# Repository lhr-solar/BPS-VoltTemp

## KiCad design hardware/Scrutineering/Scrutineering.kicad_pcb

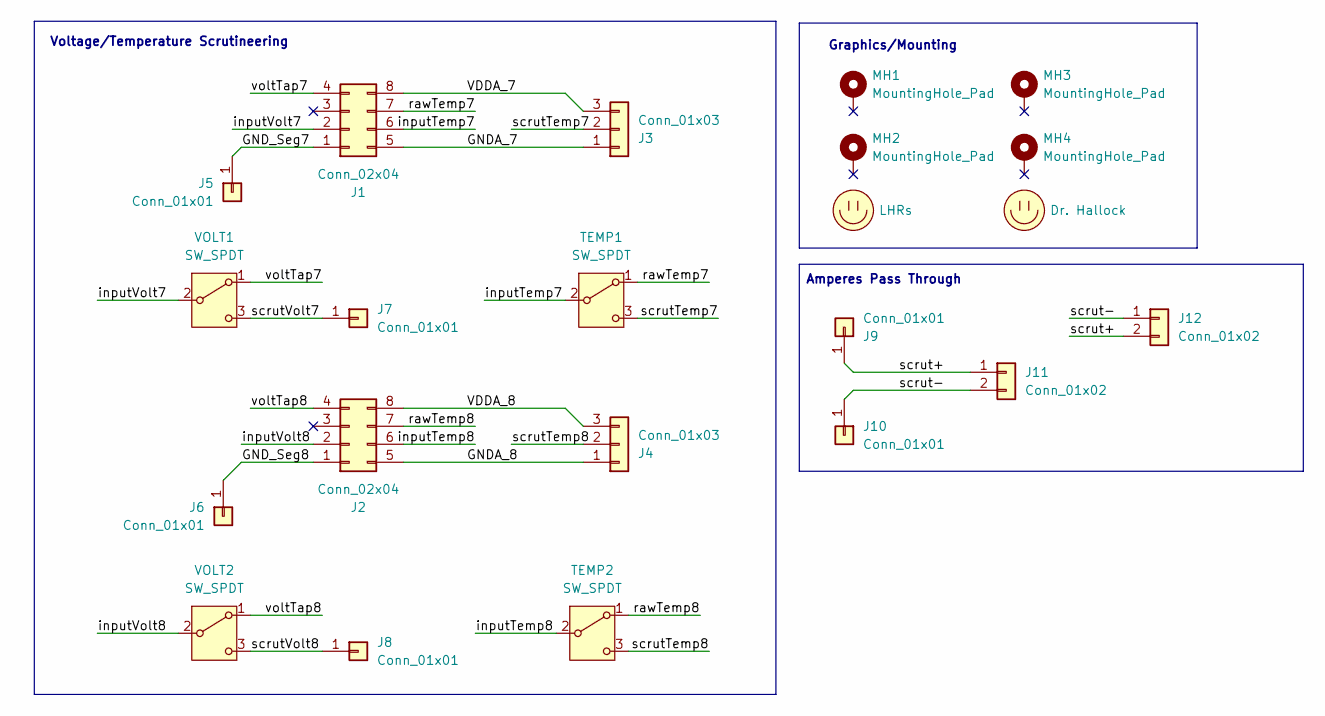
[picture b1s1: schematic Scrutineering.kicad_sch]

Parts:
J1, J2: Conn_02x04; nanofit_02x04
J3, J4: Conn_01x03; 1053131103
J5, J6, J7, J8, J9, J10: Conn_01x01; Banana_Jack_1_Pin_4mm
J11, J12: Conn_01x02; 105313-2102
LOGO1: Dr. Hallock; Hallock_Image_Small
LOGO2: LHRs; LHRs_LOGO
MH1, MH2, MH3, MH4: MountingHole_Pad; MountingHole_3.2mm_M3_Pad_TopBottom
TEMP1, TEMP2: SW_SPDT; SW_Slide_SPDT_Straight_CK_OS102011MS2Q
VOLT1, VOLT2: SW_SPDT; SW_Slide_SPDT_Straight_CK_OS102011MS2Q

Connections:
/GNDA_7: J1.5, J3.1
/GNDA_8: J2.5, J4.1
/GND_Seg7: J1.1, J5.1
/GND_Seg8: J2.1, J6.1
/VDDA_7: J1.8, J3.3
/VDDA_8: J2.8, J4.3
/inputTemp7: J1.6, TEMP1.2 (B)
/inputTemp8: J2.6, TEMP2.2 (B)
/inputVolt7: J1.2, VOLT1.2 (B)
/inputVolt8: J2.2, VOLT2.2 (B)
/rawTemp7: J1.7, TEMP1.1 (A)
/rawTemp8: J2.7, TEMP2.1 (A)
/scrut+: J9.1, J11.1, J12.2
/scrut-: J10.1, J11.2, J12.1
/scrutTemp7: J3.2, TEMP1.3 (C)
/scrutTemp8: J4.2, TEMP2.3 (C)
/scrutVolt7: J7.1, VOLT1.3 (C)
/scrutVolt8: J8.1, VOLT2.3 (C)
/voltTap7: J1.4, VOLT1.1 (A)
/voltTap8: J2.4, VOLT2.1 (A)

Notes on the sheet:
Amperes Pass Through
Voltage/Temperature Scrutineering
Graphics/Mounting

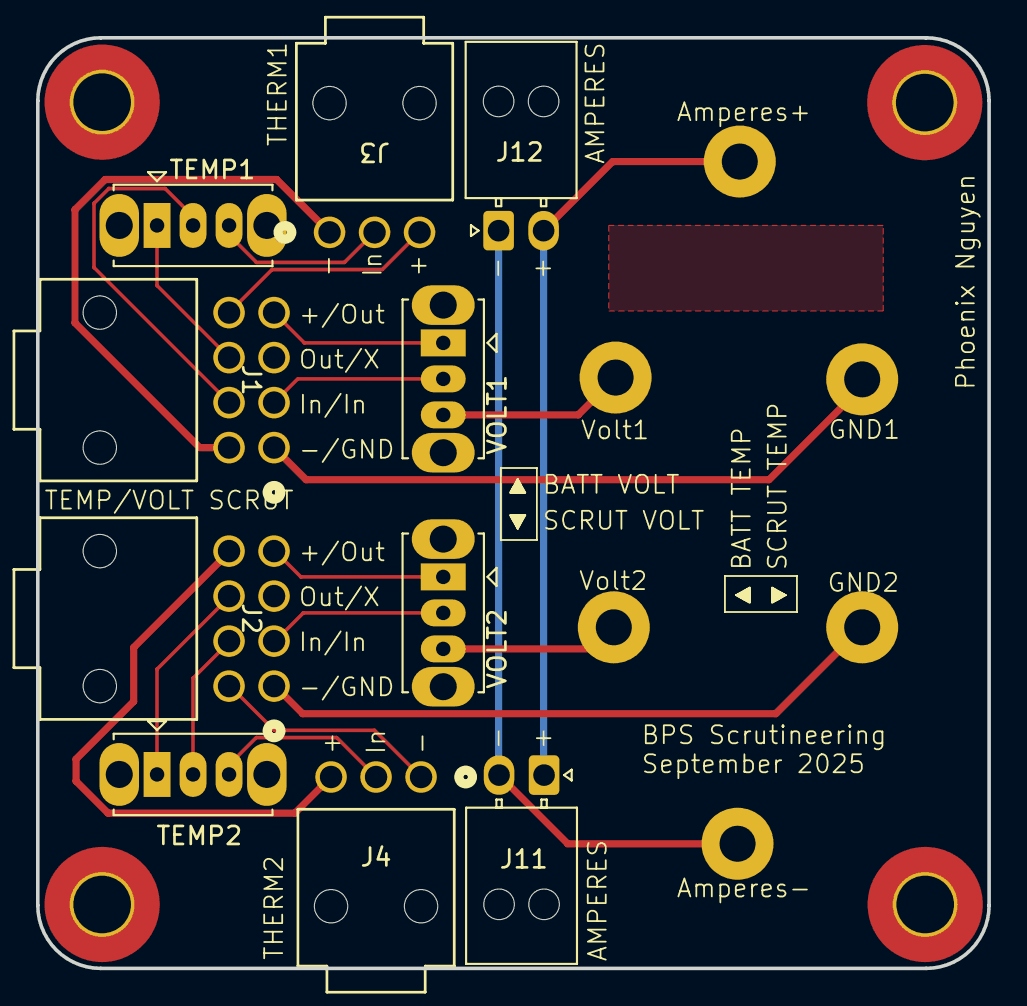
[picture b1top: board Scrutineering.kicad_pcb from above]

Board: 2 copper layers, 52.8 x 51.7 mm, 22 parts (1 on the bottom side), 20 nets.

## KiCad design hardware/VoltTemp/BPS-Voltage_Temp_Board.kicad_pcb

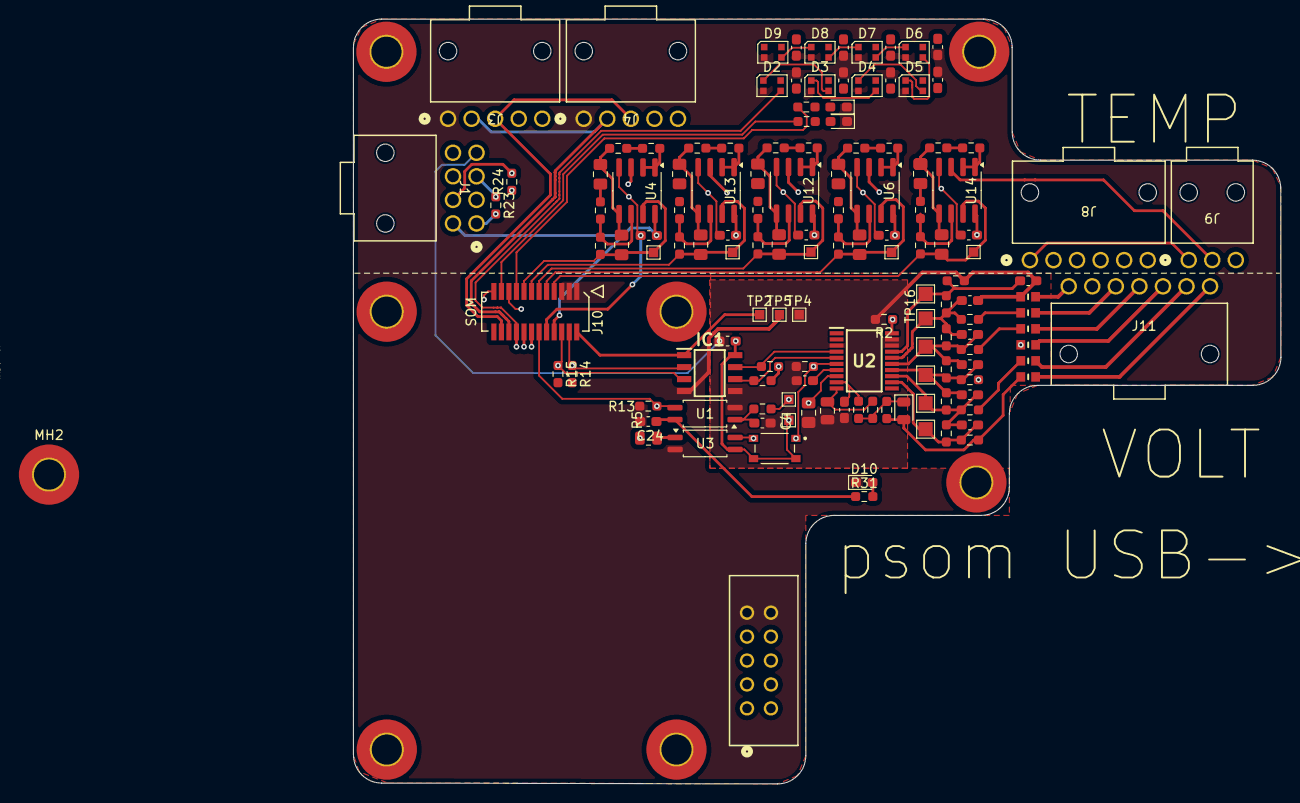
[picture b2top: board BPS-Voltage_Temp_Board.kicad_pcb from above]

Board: 4 copper layers, 98.4 x 81.2 mm, 142 parts (0 on the bottom side), 94 nets.

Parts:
C2: 10μF; C_0805_2012Metric
C3, C26, C28, C29, C32: 1uF; C_0805_2012Metric_Pad1.18x1.45mm_HandSolder
C4: 470pF; C_0603_1608Metric_Pad1.08x0.95mm_HandSolder
C5, C6, C7, C8, C9, C24, C42: 0.1uF; C_0603_1608Metric_Pad1.08x0.95mm_HandSolder
C10, C11, C12, C13, C14, C15, C16, C17: 100nF; C_0603_1608Metric_Pad1.08x0.95mm_HandSolder
C18: 4.7uF; C_0805_2012Metric_Pad1.18x1.45mm_HandSolder
C25, C27, C30, C31, C33: 1.2uF; C_0805_2012Metric_Pad1.18x1.45mm_HandSolder
C34, C35, C36, C37, C38, C39, C40, C41: 1uF; C_0603_1608Metric_Pad1.08x0.95mm_HandSolder
D1: D_Zener_Small; D_0805_2012Metric
D2, D3, D4, D5, D6, D7, D8, D9: WS2812B-2020; LED_WS2812B-2020_PLCC4_2.0x2.0mm
D10: 3v3; LED_0603_1608Metric_Pad1.05x0.95mm_HandSolder
D14: BQ-Fault; LED_0603_1608Metric_Pad1.05x0.95mm_HandSolder
D15: BQ_HB; LED_0603_1608Metric_Pad1.05x0.95mm_HandSolder
F7, F8, F9, F10, F11: 10mA; ptc_fuse_FUSC1607X75N
F12: 40mA; ptc_fuse_FUSC1607X75N
IC1: ISO1641BDR
J1: ScrutineeringConn; nanofit_02x04
J3, J4: Conn_01x05; nanofit_01x05
J5: Logic_Analyzer; CONN_SFH11-xxxC-D05-ST-XX_SUL
J8: Conn_01x06; 1053131106
J9: Conn_01x03; 1053131103
J10: 53307-2471; PeripheralSOM
J11: Conn_01x07; 1053131107
LOGO1: Dr. Hallock; Hallock_Image_Small
LOGO2: LHRs; LHRs_LOGO
MH1, MH2, MH3, MH4: MountingHole_Pad; MountingHole_3.2mm_M3_Pad_TopBottom
R1, R37, R41, R42, R49: 8.2kΩ; R_0603_1608Metric_Pad0.98x0.95mm_HandSolder
R2: 510kΩ; R_0603_1608Metric_Pad0.98x0.95mm_HandSolder
R5: 2kΩ; R_0805_2012Metric
R8, R12: 1kΩ; R_0603_1608Metric_Pad0.98x0.95mm_HandSolder
R9, R10, R11, R13, R14, R15: 10kΩ; R_0603_1608Metric_Pad0.98x0.95mm_HandSolder
R18, R19: 120; R_0603_1608Metric_Pad0.98x0.95mm_HandSolder
R23, R24, R25, R26, R27, R28, R30: 0Ω; R_0603_1608Metric_Pad0.98x0.95mm_HandSolder
R31: 4.3k; R_0603_1608Metric_Pad0.98x0.95mm_HandSolder
R34, R38, R43, R44, R50: 27kΩ; R_0603_1608Metric_Pad0.98x0.95mm_HandSolder
R35, R36, R39, R40, R45, R46, R47, R48, R51, R52: 2.7kΩ; R_0603_1608Metric_Pad0.98x0.95mm_HandSolder
R53, R54, R55, R56, R57, R58, R59, R60: 100Ω; R_0603_1608Metric_Pad0.98x0.95mm_HandSolder
SW1: BOOT; SW_TL3365AF180QG
TP1: TP_Regout; TestPoint_Pad_1.0x1.0mm
TP2, TP5: TestPoint; TestPoint_Pad_1.0x1.0mm
TP3: TP_bmsAlert; TestPoint_Pad_1.0x1.0mm
TP4: bmsGND; TestPoint_Pad_1.0x1.0mm
TP11, TP12, TP13, TP14, TP15: TP_TempOut; TestPoint_Pad_1.0x1.0mm
TP16, TP17, TP18, TP19, TP20, TP21: TestPoint; TestPoint_Pad_1.5x1.5mm
U1, U3: EL3H7
U2: BQ7692003PW
U4, U6, U12, U13, U14: TLV9062xD; SOIC-8_3.9x4.9mm_P1.27mm

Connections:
+3.3V: C10.1, C11.1, C12.1, C13.1, C14.1, C15.1, C16.1, C17.1, C24.1, D2.4 (VDD), D3.4 (VDD), D4.4 (VDD), D5.4 (VDD), D6.4 (VDD), D7.4 (VDD), D8.4 (VDD), D9.4 (VDD), IC1.1 (VCC1), J10.2 (+3.3v), R14.2, R15.2, R31.1, TP2.1, U1.4
+24V: J3.4, J4.4, J10.24 (+24V_In)
/BQ_Fault: J10.21 (SPI1_MISO), R18.1
/BQ_HB: J10.17 (SPI1_MOSI), R19.1
/I-CAN_H: J3.3, J4.3, J10.22 (CAN_H)
/I-CAN_L: J3.2, J4.2, J10.20 (CAN_L)
/LedDin: D2.3 (DIN), J5.1 (CH0), J10.18 (SPI2_SCK)
/PB3: J5.2 (CH1), J10.23 (SPI1_SCK)
/PB14: J5.5 (CH4), J10.14 (SPI2_MISO)
/PB15: J5.3 (CH2), J10.16 (SPI2_MOSI)
/ScrutineeringConn/rawTemperature4_Pre: J1.7, J8.5, R24.1
/ShieldGND: J3.5, J4.5
/TemperatureConn/rawTemperature1: J8.2, U13.3 (+)
/TemperatureConn/rawTemperature2: J8.3, U12.3 (+)
/TemperatureConn/rawTemperature3: J8.4, U6.3 (+)
/TemperatureConn/rawTemperature4: J1.6, R24.2, U4.3 (+)
/TemperatureConn/rawTemperature5: J9.2, U14.3 (+)
/TemperatureFilters/Temperature1: C31.2, J10.13 (ADC1_IN10), R48.2, TP14.1, U13.7
/TemperatureFilters/Temperature2: C30.2, J10.11 (ADC1_IN9), R47.2, TP13.1, U12.7
/TemperatureFilters/Temperature3: C27.2, J10.9 (ADC1_IN7), R40.2, TP12.1, U6.7
/TemperatureFilters/Temperature4: C25.2, J10.15 (ADC1_IN11), R36.2, TP11.1, U4.7
/TemperatureFilters/Temperature5: C33.2, J10.7 (OPAMP1_VINP), R52.2, TP15.1, U14.7
/VoltageConn/1&2COM: F11.2, R54.2
/VoltageConn/1&2COM_ext: F11.1, J11.5
/VoltageConn/2&3COM: F10.2, R55.2
/VoltageConn/2&3COM_ext: F10.1, J11.4
/VoltageConn/3&4COM: F9.2, J1.3, R23.1
/VoltageConn/3&4COM_Out: J1.1, R23.2, R56.2
/VoltageConn/3&4COM_ext: F9.1, J11.3
/VoltageConn/4&5COM: F8.2, R57.2
/VoltageConn/4&5COM_ext: F8.1, J11.2
/VoltageConn/VC0: C34.2, R25.2, R53.1, TP16.1, U2.17 (VC0)
/VoltageConn/VC1: C35.1, C36.2, R25.1, R26.2, R54.1, TP17.1, U2.16 (VC1)
/VoltageConn/VC2: C36.1, C37.2, R26.1, R30.2, R55.1, TP18.1, U2.15 (VC2)
/VoltageConn/VC3: C37.1, C38.2, R27.2, R30.1, R56.1, TP19.1, U2.14 (VC3)
/VoltageConn/VC4: C38.1, C39.2, R27.1, R28.2, R57.1, TP20.1, U2.13 (VC4)
/VoltageConn/VC5: C39.1, R28.1, R58.1, TP21.1, U2.12 (VC5)
/VoltageConn/last_cell: D1.2 (A), F7.2, R12.2, R58.2
/VoltageConn/last_cell_ext: F7.1, J11.1
/VoltageSense/ALERT: R2.1, R59.2, TP3.1, U2.20 (ALERT)
/VoltageSense/BAT: C2.2, R60.2, U2.10 (BAT)
/VoltageSense/I2C_SCL: IC1.3 (SCL1), J5.8 (CH7), J10.6 (I2C1_SCL), R15.1
/VoltageSense/I2C_SDA: IC1.2 (SDA1), J5.7 (CH6), J10.4 (I2C1_SDA), R14.1
/VoltageSense/bmSCL: IC1.6 (SCL2), R10.1, U2.5 (SCL)
/VoltageSense/bmSDA: IC1.7 (SDA2), R9.1, U2.4 (SDA)
/VoltageSense/bmsBoot: R11.2, SW1.1, U2.6 (TS1), U3.4
/VoltageSense/regout: C18.1, C42.1, IC1.8 (VCC2), R9.2, R10.2, SW1.2, TP1.1, U2.8 (REGOUT), U3.3
/bmsAlert: J5.4 (CH3), J10.12 (SPI2_NSS), R13.2, U1.3
/bmsEn: J5.6 (CH5), J10.19 (SPI1_NSS), R5.1
GND: C10.2, C11.2, C12.2, C13.2, C14.2, C15.2, C16.2, C17.2, C24.2, D2.2 (VSS), D3.2 (VSS), D4.2 (VSS), D5.2 (VSS), D6.2 (VSS), D7.2 (VSS), D8.2 (VSS), D9.2 (VSS), D10.1 (K), D14.1 (K), D15.1 (K), IC1.4 (GND1), J3.1, J4.1, J5.9 (GND), J5.10 (GND), J10.1 (GND), J10.3 (GND), J10.5 (GND), R13.1, TP5.1, U3.2
GNDA: C5.2, C6.2, C7.2, C8.2, C9.2, J1.8, J8.6, J9.3, J10.10 (GNDA), U4.4 (V-), U6.4 (V-), U12.4 (V-), U13.4 (V-), U14.4 (V-)
GND_Seg: C2.1, C4.2, C18.2, C34.1, C35.2, C40.2, C41.2, C42.2, F12.2, IC1.5 (GND2), J1.4, R2.2, R11.1, R53.2, TP4.1, U1.2, U2.3 (VSS), U2.18 (SRP), U2.19 (SRN)
unnamed: C3.2, R35.1
unnamed: C4.1, R59.1, U1.1
unnamed: C26.2, R39.1
unnamed: C28.2, R45.1
unnamed: C29.2, R46.1
unnamed: C32.2, R51.1
unnamed: D1.1 (K), R8.2, R12.1, R60.1
unnamed: D2.1 (DOUT), D3.3 (DIN)
unnamed: D3.1 (DOUT), D4.3 (DIN)
unnamed: D4.1 (DOUT), D5.3 (DIN)
unnamed: D5.1 (DOUT), D6.3 (DIN)
unnamed: D6.1 (DOUT), D7.3 (DIN)
unnamed: D7.1 (DOUT), D8.3 (DIN)
unnamed: D8.1 (DOUT), D9.3 (DIN)
unnamed: D10.2 (A), R31.2
unnamed: D14.2 (A), R18.2
unnamed: D15.2 (A), R19.2
unnamed: F12.1, J11.7
unnamed: R1.2, R34.1
unnamed: R5.2, U3.1
unnamed: R37.2, R38.1
unnamed: R41.2, R43.1
unnamed: R42.2, R44.1
unnamed: R49.2, R50.1
unnamed: C41.1, U2.7 (CAP1)
unnamed: C40.1, R8.1, U2.9 (REGSRC)
unnamed: R1.1, U4.1, U4.2 (-)
unnamed: C3.1, C25.1, R34.2, U4.5 (+)
unnamed: R35.2, R36.1, U4.6 (-)
unnamed: R37.1, U6.1, U6.2 (-)
unnamed: C26.1, C27.1, R38.2, U6.5 (+)
unnamed: R39.2, R40.1, U6.6 (-)
unnamed: R41.1, U12.1, U12.2 (-)
unnamed: C28.1, C30.1, R43.2, U12.5 (+)
unnamed: R45.2, R47.1, U12.6 (-)
unnamed: R42.1, U13.1, U13.2 (-)
unnamed: C29.1, C31.1, R44.2, U13.5 (+)
unnamed: R46.2, R48.1, U13.6 (-)
unnamed: R49.1, U14.1, U14.2 (-)
unnamed: C32.1, C33.1, R50.2, U14.5 (+)
unnamed: R51.2, R52.1, U14.6 (-)
VDDA: C5.1, C6.1, C7.1, C8.1, C9.1, J1.5, J8.1, J9.1, J10.8 (VDDA), U4.8 (V+), U6.8 (V+), U12.8 (V+), U13.8 (V+), U14.8 (V+)

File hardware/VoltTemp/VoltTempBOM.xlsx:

Reference | Value | P/N | Footprint | Qty | DNP
D15 | BQ_HB | XL-1608UBC-06A | LED_SMD:LED_0603_1608Metric_Pad1.05x0.95mm_HandSolder | 1
D10 | 3v3 | XL-1608UBC-06A | LED_SMD:LED_0603_1608Metric_Pad1.05x0.95mm_HandSolder | 1
R34,R38,R43,R44,R50 | 27k | TNPU060327K0AYEN00 | Resistor_SMD:R_0603_1608Metric_Pad0.98x0.95mm_HandSolder | 5
U4,U6,U12,U13,U14 | TLV9062xD | TLV9062QDGKRQ1 | Package_SO:SOIC-8_3.9x4.9mm_P1.27mm | 5
SW1 | BOOT | TL3365AF180QG | VoltTemp:SW_TL3365AF180QG | 1
R25,R26,R28,R30 | 0 | SFR03EZPJ000 | Resistor_SMD:R_0603_1608Metric_Pad0.98x0.95mm_HandSolder | 4
R23,R24,R27 | 0 | SFR03EZPJ000 | Resistor_SMD:R_0603_1608Metric_Pad0.98x0.95mm_HandSolder | 3
R35,R36,R39,R40,R45,R46,R47,R48,R51,R52 | 2.7k | SFR03EZPF2701 | Resistor_SMD:R_0603_1608Metric_Pad0.98x0.95mm_HandSolder | 10
J5 | Logic_Analyzer | SFH11-PBPC-D05-ST-BK | UTSVT_Connectors:CONN_SFH11-xxxC-D05-ST-XX_SUL | 1
F7,F8,F9,F10,F11 | 10mA | PTSLR06038V075 | VoltTemp:ptc_fuse_FUSC1607X75N | 5
D14 | BQ-Fault | NCD0603R1 | LED_SMD:LED_0603_1608Metric_Pad1.05x0.95mm_HandSolder | 1
C3,C26,C28,C29,C32,C34,C35,C36,C37,C38,C39,C40,C41 | 1uF | MLASU168SB5105KTNA01 | Capacitor_SMD:C_0603_1608Metric_Pad1.08x0.95mm_HandSolder,Capacitor_SMD:C_0805_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 | 13
C10,C11,C12,C13,C14,C15,C16,C17 | 100nF | MLASH168SB7104KTNA01 | Capacitor_SMD:C_0603_1608Metric_Pad1.08x0.95mm_HandSolder | 8
C5,C6,C7,C8,C9,C24,C42 | 0.1uF | MLASH168SB7104KTNA01 | Capacitor_SMD:C_0603_1608Metric_Pad1.08x0.95mm_HandSolder | 7
IC1 | ISO1641BDR | ISO1641BDR | VoltTemp:ISO1641BDR | 1
C2 | 10uF | GRM21BR61H106KE43K | Capacitor_SMD:C_0805_2012Metric | 1
F12 | 40mA | FUSC1607X75N | VoltTemp:ptc_fuse_FUSC1607X75N | 1
R53,R54,R55,R56,R57,R58,R59,R60 | 100Œ© | ESR03EZPF1000 | Resistor_SMD:R_0603_1608Metric_Pad0.98x0.95mm_HandSolder | 8
R1,R37,R41,R42,R49 | 8.2kŒ© | ERA-3AED822V | Resistor_SMD:R_0603_1608Metric_Pad0.98x0.95mm_HandSolder | 5
U1,U3 | EL3H7 | EL3H7(D)(TA)-VG | UTSVT_ICs:EL3H7 | 2
R31 | 4.3k | CRCW06034K30FKTA | Resistor_SMD:R_0603_1608Metric_Pad0.98x0.95mm_HandSolder | 1
R5 | 2k | CRCW06032K10FKEA | Resistor_SMD:R_0805_2012Metric | 1
R8,R12 | 1k | CRCW06031K00FKEI | Resistor_SMD:R_0603_1608Metric_Pad0.98x0.95mm_HandSolder | 2
R9,R10,R11,R13,R14,R15 | 10k | CRCW060310K0FKEI | Resistor_SMD:R_0603_1608Metric_Pad0.98x0.95mm_HandSolder | 6
R18,R19 | 120 | CRCW0603120RFKEC | Resistor_SMD:R_0603_1608Metric_Pad0.98x0.95mm_HandSolder | 2
R2 | 510k | CPF0603B510KE1 | Resistor_SMD:R_0603_1608Metric_Pad0.98x0.95mm_HandSolder | 1
C25,C27,C30,C31,C33 | 1.2uF | C0805C125K4RACTU | Capacitor_SMD:C_0805_2012Metric_Pad1.18x1.45mm_HandSolder | 5
U2 | BQ7692003PW | BQ7692003PW | VoltTemp:BQ7692003PW | 1
J10 | 53307-2471 | 53307-2471 | UTSVT_Connectors:PeripheralSOM | 1
D1 | D_Zener_Small | 1N448W | Diode_SMD:D_0805_2012Metric | 1
C18 | 4.7uF | 08055D475KAT4A | Capacitor_SMD:C_0805_2012Metric_Pad1.18x1.45mm_HandSolder | 1
C4 | 470pF | 06035C471J4Z2A | Capacitor_SMD:C_0603_1608Metric_Pad1.08x0.95mm_HandSolder | 1
J6,J7,J12,J13 | Conn_01x04 | 1053132104 | VoltTemp:1053132104 | 4
J11 | Conn_01x07 | 1053131107 | VoltTemp:1053131107 | 1
J8 | Conn_01x06 | 1053131106 | VoltTemp:1053131106 | 1
J9 | Conn_01x03 | 1053131103 | VoltTemp:1053131103 | 1
D2,D3,D4,D5,D6,D7,D8,D9 | WS2812B-2020 |  | LED_SMD:LED_WS2812B-2020_PLCC4_2.0x2.0mm | 8

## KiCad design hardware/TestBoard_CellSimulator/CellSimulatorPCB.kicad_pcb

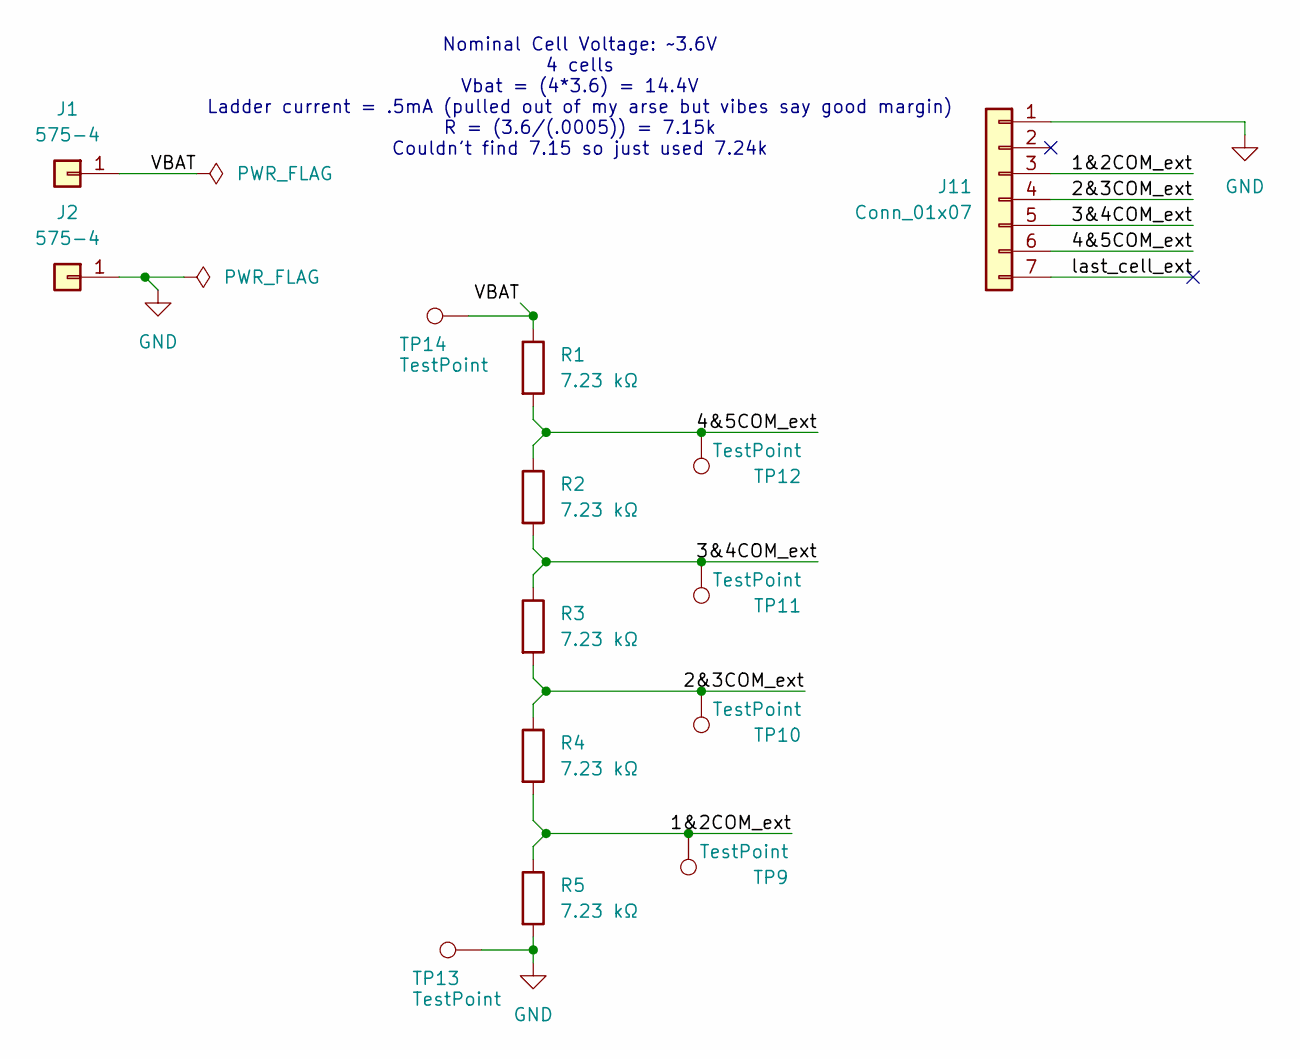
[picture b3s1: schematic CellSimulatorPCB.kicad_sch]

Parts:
J1, J2: 575-4; 5754
J11: Conn_01x07; 1053131107
R1, R2, R3, R4, R5: 7.23 kΩ; R_0603_1608Metric_Pad0.98x0.95mm_HandSolder
TP9, TP10, TP11, TP12, TP13, TP14: TestPoint; TestPoint_Keystone_5005-5009_Compact

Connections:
/1&2COM_ext: J11.3, R4.2, R5.1, TP9.1
/2&3COM_ext: J11.4, R3.2, R4.1, TP10.1
/3&4COM_ext: J11.5, R2.2, R3.1, TP11.1
/4&5COM_ext: J11.6, R1.2, R2.1, TP12.1
/VBAT: J1.1, R1.1, TP14.1
/last_cell_ext: J11.7
GND: J2.1, J11.1, R5.2, TP13.1

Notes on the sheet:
Nominal Cell Voltage: ~3.6V 4 cells Vbat = (4*3.6) = 14.4V Ladder current = .5mA (pulled out of my arse but vibes say good margin) R = (3.6/(.0005)) = 7.15k Couldn't find 7.15 so just used 7.24k

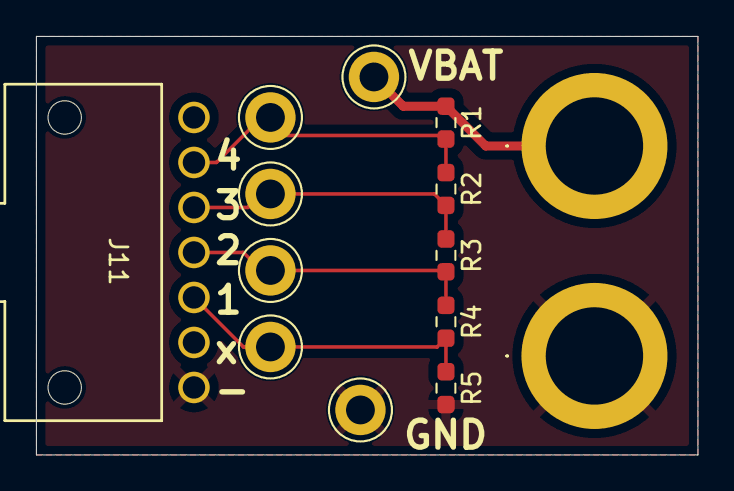
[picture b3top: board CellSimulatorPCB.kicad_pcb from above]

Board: 2 copper layers, 36.8 x 23.2 mm, 14 parts (0 on the bottom side), 6 nets.

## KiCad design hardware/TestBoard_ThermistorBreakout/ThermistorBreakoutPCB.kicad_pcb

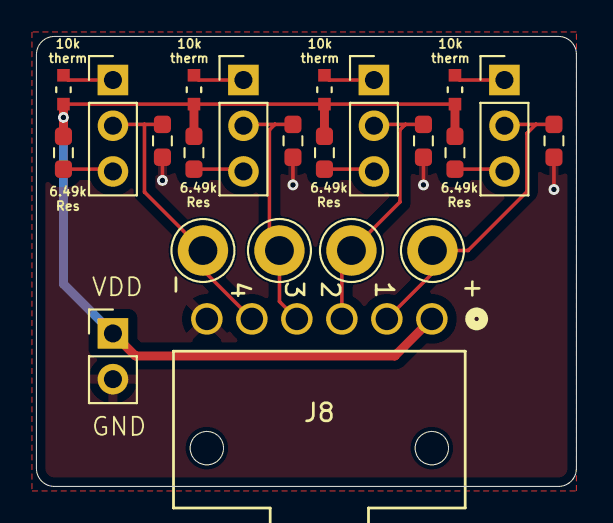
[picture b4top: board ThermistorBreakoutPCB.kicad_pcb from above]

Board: 2 copper layers, 30.0 x 25.0 mm, 22 parts (0 on the bottom side), 14 nets.

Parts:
J1: Conn_01x02; PinHeader_1x02_P2.54mm_Vertical
J3, J4, J5, J6: Conn_01x03; PinHeader_1x03_P2.54mm_Vertical
J8: Conn_01x06; 1053131106
R5, R6, R7, R8, R9, R10, R11, R12: 6.49k; R_0603_1608Metric_Pad0.98x0.95mm_HandSolder
TH5, TH6, TH7, TH8: Thermistor_NTC; THERM_ERT-J1VR104FM
TP8, TP9, TP10, TP11: TestPoint; TestPoint_Keystone_5005-5009_Compact

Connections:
/Temperature1: J3.2, J8.2, R6.1, TP11.1
/Temperature2: J4.2, J8.3, R7.1, TP10.1
/Temperature3: J5.2, J8.4, R9.1, TP8.1
/Temperature4: J6.2, J8.5, R10.1, TP9.1
GNDA: J1.2, J8.6, R6.2, R7.2, R9.2, R10.2
unnamed: J3.1, TH5.2
unnamed: J3.3, R5.1
unnamed: J4.1, TH6.2
unnamed: J4.3, R8.1
unnamed: J5.1, TH7.2
unnamed: J5.3, R11.1
unnamed: J6.1, TH8.2
unnamed: J6.3, R12.1
VDDA: J1.1, J8.1, R5.2, R8.2, R11.2, R12.2, TH5.1, TH6.1, TH7.1, TH8.1

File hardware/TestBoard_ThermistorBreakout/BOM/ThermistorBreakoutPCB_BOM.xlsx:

Reference | Qty | Value | Footprint | Datasheet | P/N
J8 | 1 | Conn_01x06 | VoltTemp:1053131106 | ~ | 1053131106
R5,R6,R7,R8,R9,R10,R11,R12 | 8 | 6.49k | Resistor_SMD:R_0603_1608Metric_Pad0.98x0.95mm_HandSolder | https://www.mouser.com/ProductDetail/YAGEO/RT0603DRE076K49L?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 | RT0603DRE076K49L
TH5,TH6,TH7,TH8 | 4 | Thermistor_NTC | UTSVT_Special:THERM_ERT-J1VR104FM | https://industrial.panasonic.com/cdbs/www-data/pdf/AUA0000/A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 | ERTJ1VR104FM

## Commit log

2025-08-20 schematic mostly done
2025-08-21 layout
2025-08-21 update embedded sharepoint submodule
2025-08-21 layout2 electric boogaloo
2025-08-21 most layout done
2025-08-21 some ocd stuff
2025-08-22 add thermistor test board, just need to route volttemp testpoints
2025-08-22 redid thermistor board
2025-08-22 forgot silkscreen
2025-08-23 add cell simulator
2025-08-23 voltage testpoints
2025-08-23 done except for nanofit footprints
2025-08-23 move one trace
2025-08-23 change 4.7pF cap to 470pF
2025-08-23 center things
2025-08-23 update connector silkscreen
2025-08-23 update cubemx
2025-08-23 fixed nanofit footprints and add labels to can in can out connectors
2025-08-23 testing push
2025-08-23 make submodule links https links so i can use ci/cd
2025-08-24 changed bild to sharepoint
2025-08-24 only check if volttemp is specified when building code
2025-08-24 playing w/ github actions
2025-08-24 poop
2025-08-25 ravi shah
2025-08-26 added some jlcpcb files
2025-08-26 volttemp gerbers
2025-09-03 Rev A (#2)
    * new folder structure
    * refactored repo
    * progress
    * added kicad-bild
    * fix footprint references
    * wrote makefile
2025-09-03 bom for cell sim and thermistor
2025-09-03 stopped displaying part numbers in schematic
2025-09-03 Bom (#3)
    * bom
    * bom for cell sim and thermistor
    * stopped displaying part numbers in schematic
2025-09-09 fix diode and last fuse p/n
2025-09-09 fix diode and last fuse p/n (#4)
2025-09-14 initial schematic and layout
2025-09-18 updated layout
2025-09-18 schematic with graphics/mounting
2025-09-18 graphics stuff
2025-09-18 fixed routing
2025-09-20 BOM and gerber (still need to find jack P/N)
2025-09-20 final
2025-09-20 revert back to main...
2025-09-20 this is the staircase board :(
2025-09-20 I added the 3d models for the connectors. Need to swap layers around some
2025-09-22 added Scrutineering footprints
2025-09-22 added Scrutineering 3d models
2025-09-22 BOM and gerber with changed connector
2025-09-22 Scrutineering (#5)
    * initial schematic and layout
    * updated layout
    * schematic with graphics/mounting
    * graphics stuff
    * fixed routing
    * BOM and gerber (still need to find jack P/N)
2025-09-27 Traces finished, passes DRC, need to complete silkscreen
2025-09-27 Initial board done. Labels on everything, yay
2025-09-27 Goofy pictures and names added
2025-09-27 goofy things
2025-10-02 Review Council concerns have been dealt with :-)
2025-10-05 Boot switch changed to V_Boot, ShieldGND added to scrut conn, labels added to LEDs, misc routing tweaks
2025-10-05 i tweaked one more thing :)
2025-10-10 V-Boot resistors adjusted, ranges safely from 1.8 to 5.8 volts
2025-10-11 lakshay concerns dealt with and also i did the jlcpcb generation thing
2025-10-11 i fixed the clearance violation :-)
